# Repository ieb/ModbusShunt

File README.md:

# Modbus Battery Sensor.

Mk1 used the ADC on an Attiny3224. Fine for voltage but not really accurate enough for low levels of current on a 75mV 100A shunt. 

This version is built arround a INA219 which is far easier to use. It speaks modbus to communicate with a modbus controller that can control if its on or not.

The controller will be a Attiny or ESP32 driving a eInk display depending. This will only be on when the boat is in service.

A BLE version was created, but in the end I felt it was overcomplicated and would need to deep sleep to avoid draining the battery.

The device speaks Modbus RTU, 9600 baud, 8N1.

# Holding registers

|| Register || type || units per bit || R/W || description ||
| 0 | int16 | serial number | R | serial number, can be written once only |
| 1 | int16 | device address | R/W | modbus unit or device address |
| 2 | int16 | A | R/W | Shunt full scale current range, default 100A |
| 3 | int16 | mV | R/W | Shunt full scale voltage, default 75mV |
| 4 | int16 | 0.1C | R/W | Temperature probe 1 offset, default 0 |
| 5 | int16 | 0.001x | R/W | Temperature probe 1 scale, default 1000 eg 1x |
| 6 | int16 | 0.1C | R/W | Temperature probe 2 offset, default 0 |
| 7 | int16 | 0.001x | R/W | Temperature probe 2 scale, default 1000 eg 1x |

# Input registers

|| Register || type || units per bit || description ||
|  0   | int16 | mV | Battery voltage |
|  1   | int16 | 0.1 A | Shunt current |
|  2   | int16 | 0.01 C | Temperature probe 1 |  
|  3   | int16 | 0.01 C | Temperature probe 2 |  
|  4   | int16 | bitmap | Lower 8 bits are Serial documented [here](https://github.com/SpenceKonde/megaTinyCore/blob/master/megaavr/extras/Ref_Serial.md#serialgetstatus) bit 8 indicates and error reading voltage, bit 9 indicates and error reading current  |
|  5   | int16 | mV | MCU Supply voltage |
|  6   | int16 | 0.1 C | MCU Temperature |
|  1000  | int16 | counter | modbus frames recieved |
|  1001   | int16 | counter | modbus frames sent |
|  1002   | int16 | counter | modbus errors recieved |
|  1003   | int16 | counter | modbus frames ignored |
|  1004   | int16 | counter | modbus errors sent |
|  1005   | int16 | counter | modbus buffer overflow |

# megaTinyCore 

This code needs megaTiny core 2.6.4 to work as there are some timing bugs that cause it to fail with the default platform IO 2.5.11 version. Upgrading is a pain as it requires installing a custom package. Installs from github fail as the layout of the source repo is wrong and missing files. 

The hacky way is to install manually as its not possible to install from a git repo due to a bug in the pio code that parses versions numbers.

		cd ~/src
		git clone https://github.com/SpenceKonde/megaTinyCore.git
		cd megaTinyCore
		git co -b 2.6.4
		mkdir ~/.platformio/packages/framework-arduino-megaavr-megatinycore@2.6.4
		cd ~/.platformio/packages/framework-arduino-megaavr-megatinycore@2.6.4
		cat << EOF > .piopm
		{"type": "tool", "name": "framework-arduino-megaavr-megatinycore", "version": "2.6.4", "spec": {"owner": "platformio", "id": 11448, "name": "framework-arduino-megaavr-megatinycore", "requirements": null, "uri": null}}
		EOF
		cat << EOF > package.json
		{
		  "name": "framework-arduino-megaavr-megatinycore",
		  "version": "2.6.4",
		  "description": "Arduino Wiring-based Framework for Microchip tinyAVR 0-series and 1-series chips (megaTinyCore)",
		  "keywords": [
		    "framework",
		    "arduino",
		    "microchip",
		    "tinyAVR"
		  ],
		  "repository": {
		    "type": "git",
		    "url": "https://github.com/ieb/megaTinyCore"
		  }
		}
		EOF
		ln -s ~/megaTinyCore/megaavr/* .
		ln -s ~/megaTinyCore/ChangeLog.md .
		ln -s ~/megaTinyCore/Installation.md .
		ln -s ~/megaTinyCore/MakeUPDIProgrammer.md .
		ln -s ~/megaTinyCore/README.md .
		ln -s ~/megaTinyCore/Wiring.md .

# ToDo

* [x] Basic implementation, with modbus, holding registers and input registers.
* [x] Implement test client
* [x] Reimplement modbus frame handling
* [x] Implement sleep mode, wake on frame
* [x] Average current and voltage over time period, eg 30s
* [x] Test frame handling of packets for other units.
* [x] Calibrate NTC sensors.
* [ ] Test write to holding registers.
* [ ] Implement current monitoring with auto scaling for different ranges using features of the INA219

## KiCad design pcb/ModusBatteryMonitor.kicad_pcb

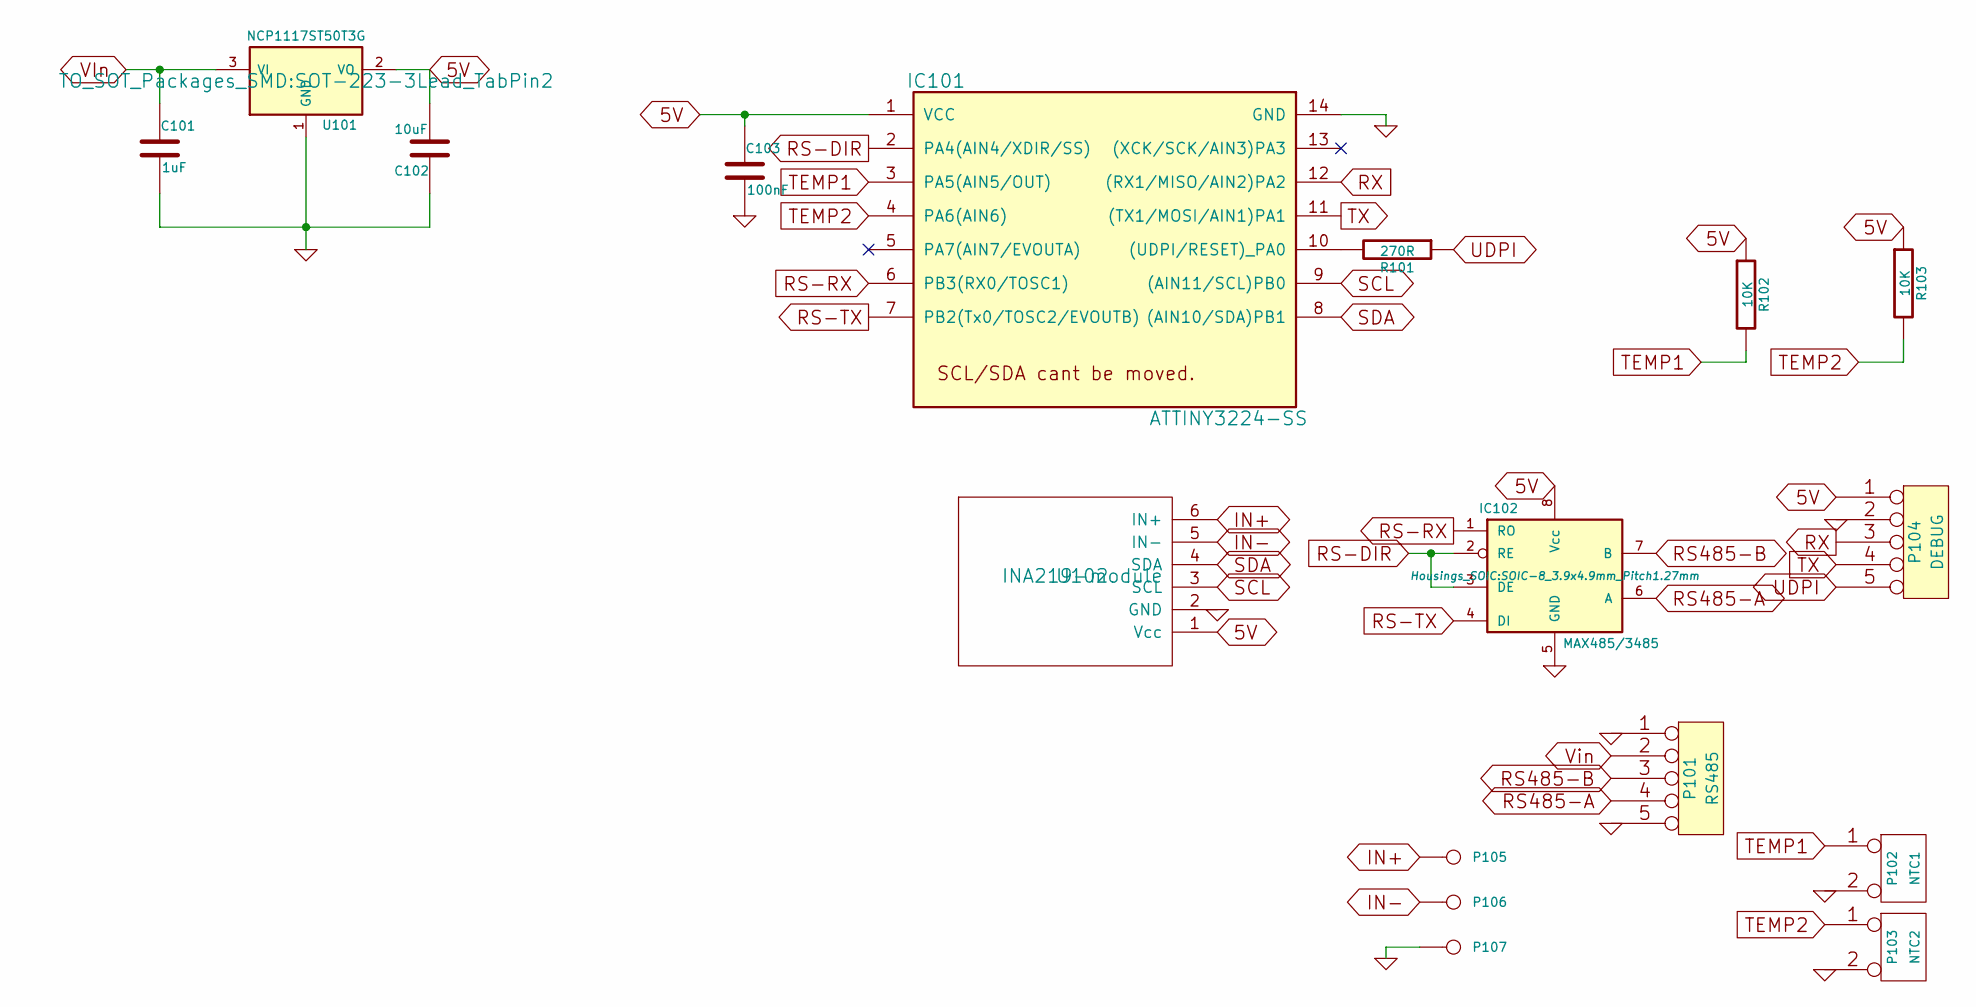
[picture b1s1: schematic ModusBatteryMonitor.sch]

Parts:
C101: 1uF; C_1206
C102: 10uF; C_0805
C103: 100nF; C_0805
IC101: ATTINY3224-SS; SOIC-14_3.9x8.7mm_Pitch1.27mm
IC102: MAX485/3485; SOIC-8_3.9x4.9mm_Pitch1.27mm
P101: RS485; Wago250PushSocket5way
P102: NTC1; Pin_Header_Straight_1x02
P103: NTC2; Pin_Header_Straight_1x02
P104: DEBUG; Pin_Header_Straight_1x05
P105: SHUNT+; M5Bolt
P106: SHUNT-; M5Bolt
P107: BAT-; Pin_Header_Straight_1x01
R101: 270R; R_0805
R102, R103: 10K; R_0805
U101: NCP1117ST50T3G; SOT-223-3Lead_TabPin2
U102: INA219-module; INA219Module

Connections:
5V: C102.2, C103.1, IC101.1 (VCC), IC102.8 (Vcc), P104.1, R102.1, R103.1, U101.2 (VO), U102.1 (Vcc)
GND: C101.2, C102.1, C103.2, IC101.14 (GND), IC102.5 (GND), P101.1, P101.5, P102.2 (PM), P103.2 (PM), P104.2, P107.1, U101.1 (GND), U102.2 (GND)
IN+: P105.1, U102.6 (IN+)
IN-: P106.1, U102.5 (IN-)
unnamed: IC101.10 ((UDPI/RESET)_PA0), R101.2
RS485-A: IC102.6 (A), P101.4
RS485-B: IC102.7 (B), P101.3
RS-DIR: IC101.2 (PA4(AIN4/XDIR/SS)), IC102.2 (RE), IC102.3 (DE)
RS-RX: IC101.6 (PB3(RX0/TOSC1)), IC102.1 (RO)
RS-TX: IC101.7 (PB2(Tx0/TOSC2/EVOUTB)), IC102.4 (DI)
RX: IC101.12 ((RX1/MISO/AIN2)PA2), P104.3
SCL: IC101.9 ((AIN11/SCL)PB0), U102.3 (SCL)
SDA: IC101.8 ((AIN10/SDA)PB1), U102.4 (SDA)
TEMP1: IC101.3 (PA5(AIN5/OUT)), P102.1, R102.2
TEMP2: IC101.4 (PA6(AIN6)), P103.1, R103.2
TX: IC101.11 ((TX1/MOSI/AIN1)PA1), P104.4
UDPI: P104.5, R101.1
VIn: C101.1, P101.2, U101.3 (VI)

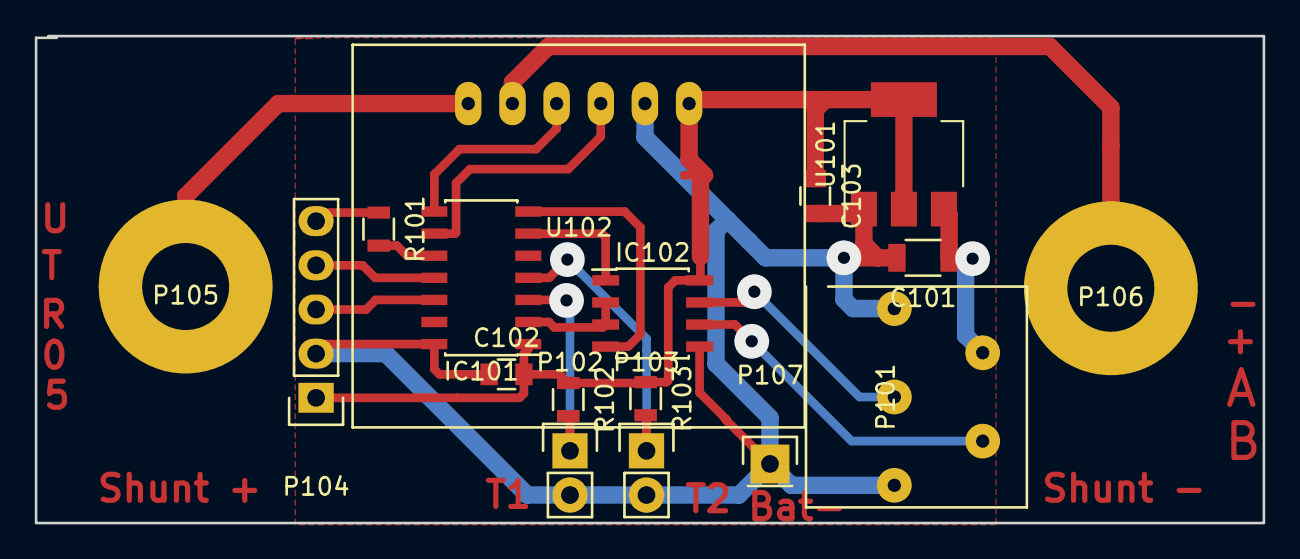
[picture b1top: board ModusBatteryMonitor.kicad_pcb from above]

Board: 2 copper layers, 70.6 x 28.0 mm, 17 parts (0 on the bottom side), 18 nets.

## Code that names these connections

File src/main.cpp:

#include <Arduino.h>
#include <Wire.h>

// Holding registers, used by command line, and the modbus holding 
// register class. Must be defined before including.

#define REG_SERIAL_NUMBER 0
#define REG_DEVICE_ADDRESS 1
#define REG_SHUNT_RANGE_CURRENT 2
#define REG_SHUNT_RANGE_VOLTAGE 3
#define REG_TEMPERATURE1_OFFSET 4
#define REG_TEMPERATURE1_SCALE 5
#define REG_TEMPERATURE2_OFFSET 6
#define REG_TEMPERATURE2_SCALE 7
#define NUMBER_REGISTERS 8


#include <avr/sleep.h>
#include "commandline.h"
#include "ina219.h"
#include "ntcsensor.h"
#include "modbus.h"
#include "oled.h"


extern int16_t readVoltage();
extern int16_t readCurrent();
extern int16_t readTemperature(int8_t ch);
extern int16_t readMCUVoltage();
extern int16_t readMCUTemperature();
extern CommandLine commandLine;
int16_t errorBitmap = 0x00;

// MAX485 is on RX0/TX0 Serial, TX0==PB2 pin 7, RX0=PB3 pin 6
// XDIR low to recieve, high to send on PA4 pin 4
// Debug header is on Serial1

#define rs485 Serial
#define debug Serial1


class InputRegisterImpl : public InputRegisters {
	public:
		bool hasRegister(int16_t reg) {
			return ( reg >= 0 && reg <=6 );
		}	
		int16_t getRegister(int16_t reg) {
			int16_t value = 0;
			switch(reg) {
				case 0:
					value = readVoltage();
					break;
				case 1:
					value = readCurrent();
					break;
				case 2:
					value = readTemperature(0);
					break;
				case 3: 
					value = readTemperature(1);
					break;
				case 4: 
					value = (errorBitmap & 0xFF00) | rs485.getStatus();
					break;
				case 5:
					value =  readMCUVoltage();
					break;
				case 6:
					value = 100*readMCUTemperature();
					break;

			}
			return value;
		};
};
// pins
#define TEMP_NTC1_PIN PIN_PA5  // hardware pin 3
#define TEMP_NTC2_PIN PIN_PA6  // hardware pin 4


InputRegisterImpl inputRegisters = InputRegisterImpl();
HoldingRegisters holdingRegisters = HoldingRegisters(NUMBER_REGISTERS);
Modbus modbus = Modbus(&rs485, &debug, &holdingRegisters, &inputRegisters);
Ina219 ina219(&debug);
CommandLine commandLine(&debug, &holdingRegisters, &inputRegisters);
NtcSensor ntcSensor(&debug);
Oled oled;

float averageVoltage = 0;
float averageCurrent = 0;

// must be volatile so the compiler doesnt optimnise
bool ina219Ok = true;


/*
// see https://github.com/SpenceKonde/megaTinyCore/blob/e59fc3046dd69f951497506e8f441a6818c28be5/megaavr/extras/Ref_PinInterrupts.md
// Used to detect wake up from sleep.
ISR(PORTA_PORT_vect) {
	byte flags = VPORTA.INTFLAGS;
	// wake up pin is pin PA 6
	if (flags & (1 << 6) ) {
		shouldWakeUp=true;
		VPORTA.INTFLAGS |= (1 << 6); // clear the flag, so it doesnt fire continuously.
	}
}
*/


int16_t readMCUVoltage() {
    analogReference(INTERNAL1V024);
    delayMicroseconds(100);
    int32_t vddmeasure = analogReadEnh(ADC_VDDDIV10, 12); // Take it at 12 bits
    vddmeasure *= 10; // since we measured 1/10th VDD
    int16_t returnval = vddmeasure >> 2; // divide by 4 to get into millivolts.
    if (vddmeasure & 0x02) {
        // if last two digits were 0b11 or 0b10 we should round up
        returnval++;
    }
    return returnval;
}

int16_t readMCUTemperature() {
    int8_t sigrowOffset = SIGROW.TEMPSENSE1;
    uint8_t sigrowGain = SIGROW.TEMPSENSE0;
    analogSampleDuration(128); // must be >= 32µs * f_CLK_ADC per datasheet 30.3.3.7
    analogReference(INTERNAL1V024);
    uint32_t reading = analogRead(ADC_TEMPERATURE);
    reading -= sigrowOffset;
    reading *= sigrowGain;
    reading += 0x80; // Add 1/2 to get correct rounding on division below
    reading >>= 8; // Divide result to get Kelvin
    return reading - 273; // return in C

}

void readSensors() {
		int16_t voltage = (int16_t)(1000.0*ina219.getVoltage());
		// 10mA per bit 320A  0.01*32000
	  int16_t current = (int16_t)(100*ina219.getCurrent());
		// temperature 0.01C per bit, 320C max
		int16_t temp1 = ntcSensor.getTemperature(0);
		int16_t temp2 = ntcSensor.getTemperature(1);
		uint16_t tons = millis()/1000;

		debug.print(F(" v="));debug.print(voltage);
		debug.print(F(" mV c="));debug.print(current);
		debug.print(F(" 10mA t1="));debug.print(temp1);
		debug.print(F(" 0.01C t2="));debug.print(temp2);
		debug.print(F(" 0.01C tons="));debug.print(tons);
		debug.println("");

}

void dumpModbusStatus() {
	modbus.dumpStatus();
}






void setup() {

  // Open serial communications and wait for port to open:
  debug.begin(115200);

  // try 115200, if that fails drop back to 9600 and set.


  if ( ina219.begin() != I2C_OK) {
  	ina219Ok = false;
	  debug.print(F("Failed to find INA219 chip, error:"));
	  debug.println(ina219.getError());
  }
  commandLine.begin();

  modbus.setDeviceAddress(commandLine.deviceAddress);
  modbus.begin();

  ntcSensor.addSensor(TEMP_NTC1_PIN, 0);
  ntcSensor.addSensor(TEMP_NTC2_PIN, 1);
  ntcSensor.begin();

  oled.begin();

  commandLine.diagnosticsEnabled = false;


	 if (!ina219Ok) {
	 	 debug.println(F("INA219 not responding"));
	 }
	 debug.println(F("Press h for help menu"));

	 // setup sleep mode
	 set_sleep_mode(SLEEP_MODE_STANDBY);
	 sleep_enable();

}

int16_t readVoltage() {
	return (int16_t)(1000.0*averageVoltage);;
}
int16_t readCurrent() {
	return  (int16_t)(100*averageCurrent);
}

int16_t readTemperature(int8_t ch) {
	return ntcSensor.getTemperature(ch);
}


void readShunt() {
	static unsigned long lastRead = 0;
	unsigned long now = millis();
	if ((now - lastRead) > 5000 ) {
		float voltage = ina219.getVoltage();
		float current = ina219.getCurrent();
		int16_t temp1 = readTemperature(0);
		int16_t temp2 = readTemperature(1);


		if ( lastRead == 0 ) {
				averageVoltage = voltage;
				averageCurrent = current;
		}
		lastRead = now;
		averageVoltage = averageVoltage*0.9 + voltage*0.1;
		if ( ina219.getError() != I2C_OK) {
			errorBitmap |= 0x0100;
		} else {
			errorBitmap &= 0xFDFF;
		}
		averageCurrent = averageCurrent*0.9 + current*0.1;
		if ( ina219.getError() != I2C_OK) {
			errorBitmap |= 0x0200;
		} else {
			errorBitmap &= 0xFDFF;
		}

		oled.voltage = 100*voltage;
		oled.current = 100*current;
		oled.temp1 = temp1;
		oled.temp2 = temp2;
		oled.update();

	}
}


void powerDownSleep() {
		ina219.powerDown(true);
		oled.powerDown(true);

		//USART0.STATUS &= ~(1<< 4); // enable RXSIF (Rx start frame interupt flag)
		USART0.CTRLB |= 1<<4; // set the SFDEN bit, start of frame detection.
		//USART1.STATUS &= ~(1<< 4); // enable RXSIF (Rx start frame interupt flag)
		USART1.CTRLB |= 1<<4; // set the SFDEN bit, start of frame detection.
		sleep_cpu();
		// Not required, RX clears it. USART0.CTRLB != 1<<4; // clear the SFDEN bit, start of frame detection.
		ina219.powerDown(false);
		oled.powerDown(false);

}



void loop() {
	static unsigned long lastActivity = millis();
  unsigned long now = millis(); 
  readShunt();

  if ( commandLine.checkCommand() ) {
  	lastActivity = now;  	
  }
  modbus.setDiagnostics(commandLine.diagnosticsEnabled);
  if ( modbus.readQuery() ) {
  	oled.messages++;
  	lastActivity = now;
  }
  if ( (now - lastActivity) > 60000  ) {
  	debug.println(F("sleeping"));
  	debug.flush();
  	powerDownSleep();
  	debug.println(F("wakeup"));
  	lastActivity = millis();
  }
}

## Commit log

2022-12-21 Initial version
2022-12-24 Modbus tested and working for read.
2022-12-24 Cleanup
2022-12-26 Added better Modbus RTU frame handling, sleep and tests
2023-01-01 Made housing
2023-01-02 Fixed NtC sensors and adjusted LUT
2023-01-15 Added OLED display
